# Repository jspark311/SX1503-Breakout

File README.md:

# SX1503-Breakout

A breakout board for the Semtech i2c GPIO expander. The SX1503 is an i2c GPIO expander with support for 16 extra pins, 2 voltage translation banks, and a simple PLD capability.

#### [Hackaday.io Page](https://hackaday.io/project/168368-sx1503-breakout)

#### [Order from Tindie](https://www.tindie.com/products/18522/)

#### [Arduino driver](https://github.com/jspark311/Arduino-SX150x)

------------------------

### What is in this repository:

**./doc**:  Location for documentation

**./KiCAD**:  Hardware design files

**./Arduino**:  Arduino driver

------------------------

Front | Back
:-------:|:------:
  |

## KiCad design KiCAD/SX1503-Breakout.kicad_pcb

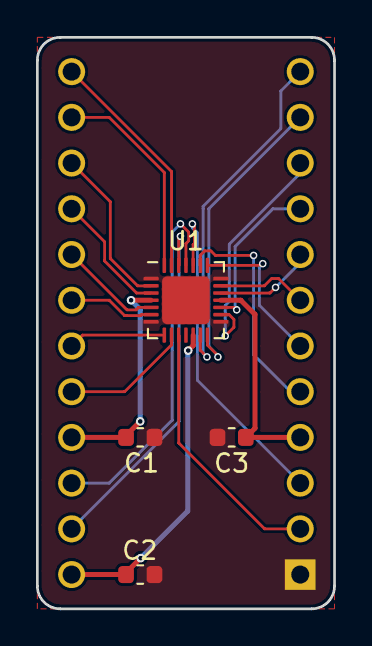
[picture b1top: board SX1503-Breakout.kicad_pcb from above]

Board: 2 copper layers, 16.5 x 31.8 mm, 6 parts (1 on the bottom side), 24 nets.

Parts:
C1, C3: 10uF; C_0603_1608Metric
C2: 1uF; C_0603_1608Metric
J1, J2: Conn_01x12_Male; PinHeader_1x12_P2.54mm_Vertical
U1: SX1503; QFN-28-1EP_4x4mm_P0.4mm_EP2.4x2.4mm

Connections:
/GND: C1.2, C2.2, C3.2, J2.12, U1.1, U1.7, U1.15, U1.21, U1.29
/IO-0: J1.12, U1.27
/IO-1: J1.11, U1.28
/IO-2: J1.10, U1.2
/IO-3: J1.9, U1.3
/IO-4: J1.8, U1.5
/IO-5: J1.7, U1.6
/IO-6: J1.6, U1.8
/IO-7: J1.5, U1.9
/IO-8: J2.1, U1.13
/IO-9: J2.2, U1.14
/IO-10: J2.3, U1.16
/IO-11: J2.4, U1.17
/IO-12: J2.5, U1.19
/IO-13: J2.6, U1.20
/IO-14: J2.7, U1.22
/IO-15: J2.8, U1.23
/SCL: J1.2, U1.26
/SDA: J1.3, U1.25
/Vcc: C2.1, J1.1, U1.12
/Vcc1: C1.1, J1.4, U1.4
/Vcc2: C3.1, J2.9, U1.18
/~INT: J2.11, U1.10
/~RESET: J2.10, U1.24

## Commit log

2019-11-02 Initial commit.
2019-11-02 Adding OSHPark renders.
2019-11-09 Updating README, adding datasheet.
2019-11-20 First commit of Arduino driver. Doesn't build yet.
2019-11-24 Arduino driver works correctly.
2019-12-04 Ground work for bus abstraction. Example sketch improvements. Serialize() implementation.
2019-12-04 CRLF purge.
2019-12-04 Documentation.
2019-12-05 Carity improvement.
2019-12-15 Fixed two inobvious scoping bugs.
2020-02-22 Arduino driver is now in the Library manager.
